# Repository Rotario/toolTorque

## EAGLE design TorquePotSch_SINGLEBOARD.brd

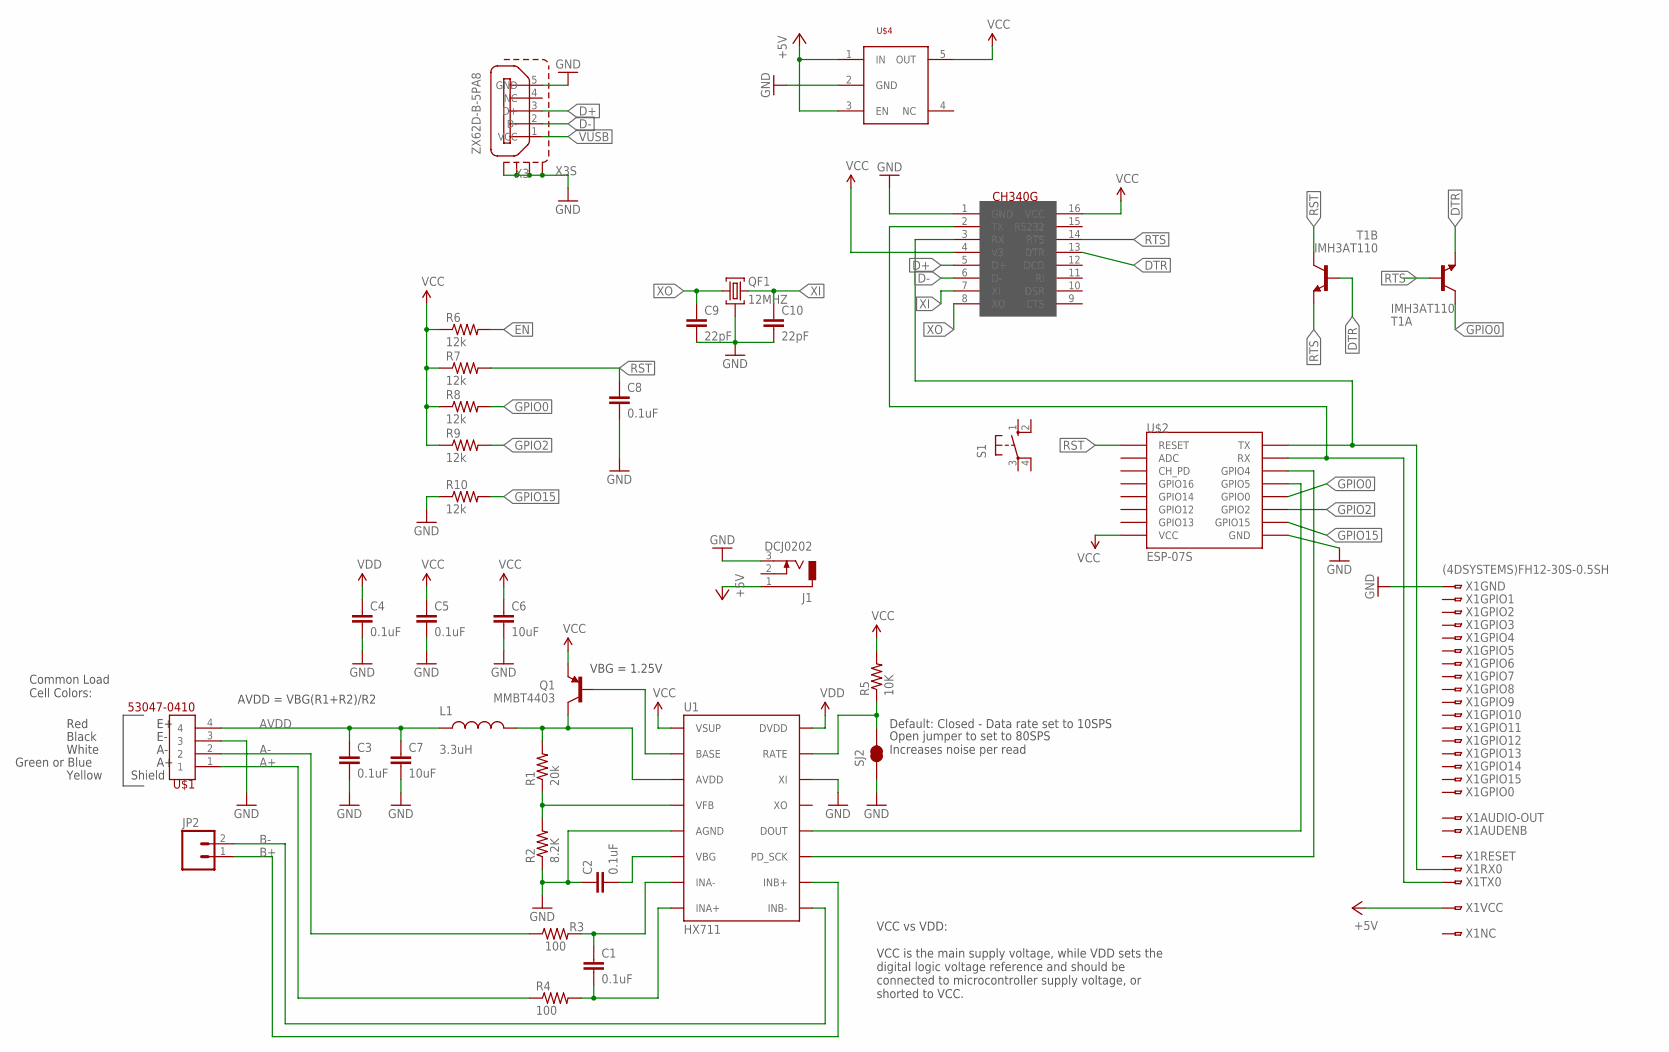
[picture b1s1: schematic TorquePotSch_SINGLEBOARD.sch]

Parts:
C1, C2, C3, C4, C5, C8: 0.1uF; 0603-CAP
C6, C7: 10uF; 1210
C9, C10: 22pF; 0603-CAP
J1: DCJ0202
JP2: M02PTH; 1X02
L1: 3.3uH; 0805
Q1: MMBT4403; SOT23-3
QF1: 12MHZ; HC49U
R1: 20k; 0603-RES
R2: 8.2K; 0603-RES
R3, R4: 100; 0603-RES
R5: 10K; 0603-RES
R6, R7, R8, R9, R10: 12k; R0805
S1: 10-XX; B3F-10XX
SJ2: JUMPER-PAD-2-NC_BY_TRACE; PAD-JUMPER-2-NC_BY_TRACE_YES_SILK
T1: IMH3AT110; SMT6
U1: HX711; SO16
U$1: 53047-0410
U$2: ESP-07S; ESP07S
U$3: CH340G; SOIC16
U$4: TLV755P; SOT23-5L
X1: (4DSYSTEMS)FH12-30S-0.5SH; FH12-30S-0.5SH
X3: ZX62D-B-5PA8

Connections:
+5V: J1.1, U$4.1 (IN), U$4.3 (EN), X1.26, X1.27
A+: R4.1, U$1.1
A-: R3.1, U$1.2
AVDD: C3.1, C7.1, L1.1, U$1.4
B+: JP2.1, U1.10 (INB+)
B-: JP2.2, U1.9 (INB-)
D+: U$3.5 (D+), X3.3 (D+)
D-: U$3.6 (D-), X3.2 (D-)
DTR: T1.6 (E), U$3.13 (DTR)
EN: R6.2
GND: C2.1, C3.2, C4.2, C5.2, C6.2, C7.2, C8.2, C9.2, C10.2, J1.3, QF1.2, R2.1, R10.1, SJ2.1, U1.5 (AGND), U1.14 (XI), U$1.3, U$2.GND, U$3.1 (GND), U$4.2 (GND), X1.1, X1.21, X1.25, X1.30, X3.5 (GND), X3.S1, X3.S2, X3.S3, X3.S4
GPIO0: R8.2, T1.1 (C), U$2.GPIO0
GPIO2: R9.2, U$2.GPIO2
GPIO15: R10.2, U$2.GPIO15
unnamed: R5.1, SJ2.2, U1.15 (RATE)
unnamed: C1.1, R3.2, U1.7 (INA-)
unnamed: C1.2, R4.2, U1.8 (INA+)
unnamed: Q1.1 (B), U1.2 (BASE)
unnamed: L1.2, Q1.3 (C), R1.2, U1.3 (AVDD)
unnamed: R1.1, R2.2, U1.4 (VFB)
unnamed: C2.2, U1.6 (VBG)
unnamed: U1.12 (DOUT), U$2.GPIO5
unnamed: U1.11 (PD_SCK), U$2.GPIO4
unnamed: U$2.TX, U$3.3 (RX), X1.23
unnamed: U$2.RX, U$3.2 (TX), X1.24
RST: C8.1, R7.2, U$2.REST (RESET)
RTS: U$3.14 (RTS)
VCC: C5.1, C6.1, Q1.2 (E), R5.2, R6.1, R7.1, R8.1, R9.1, U1.1 (VSUP), U$2.VCC, U$3.4 (V3), U$3.16 (VCC), U$4.5 (OUT)
VDD: C4.1, U1.16 (DVDD)
VUSB: X3.1 (VCC)
XI: C10.1, QF1.3, U$3.7 (XI)
XO: C9.1, QF1.1, U$3.8 (XO)

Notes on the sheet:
VBG = 1.25V
AVDD = VBG(R1+R2)/R2
Default: Closed - Data rate set to 10SPS
Open jumper to set to 80SPS Increases noise per read
Red
Black
White
Green or Blue
Common Load Cell Colors:
Shield
Yellow
VCC vs VDD: VCC is the main supply voltage, while VDD sets the digital logic voltage reference and should be connected to microcontroller supply voltage, or shorted to VCC.

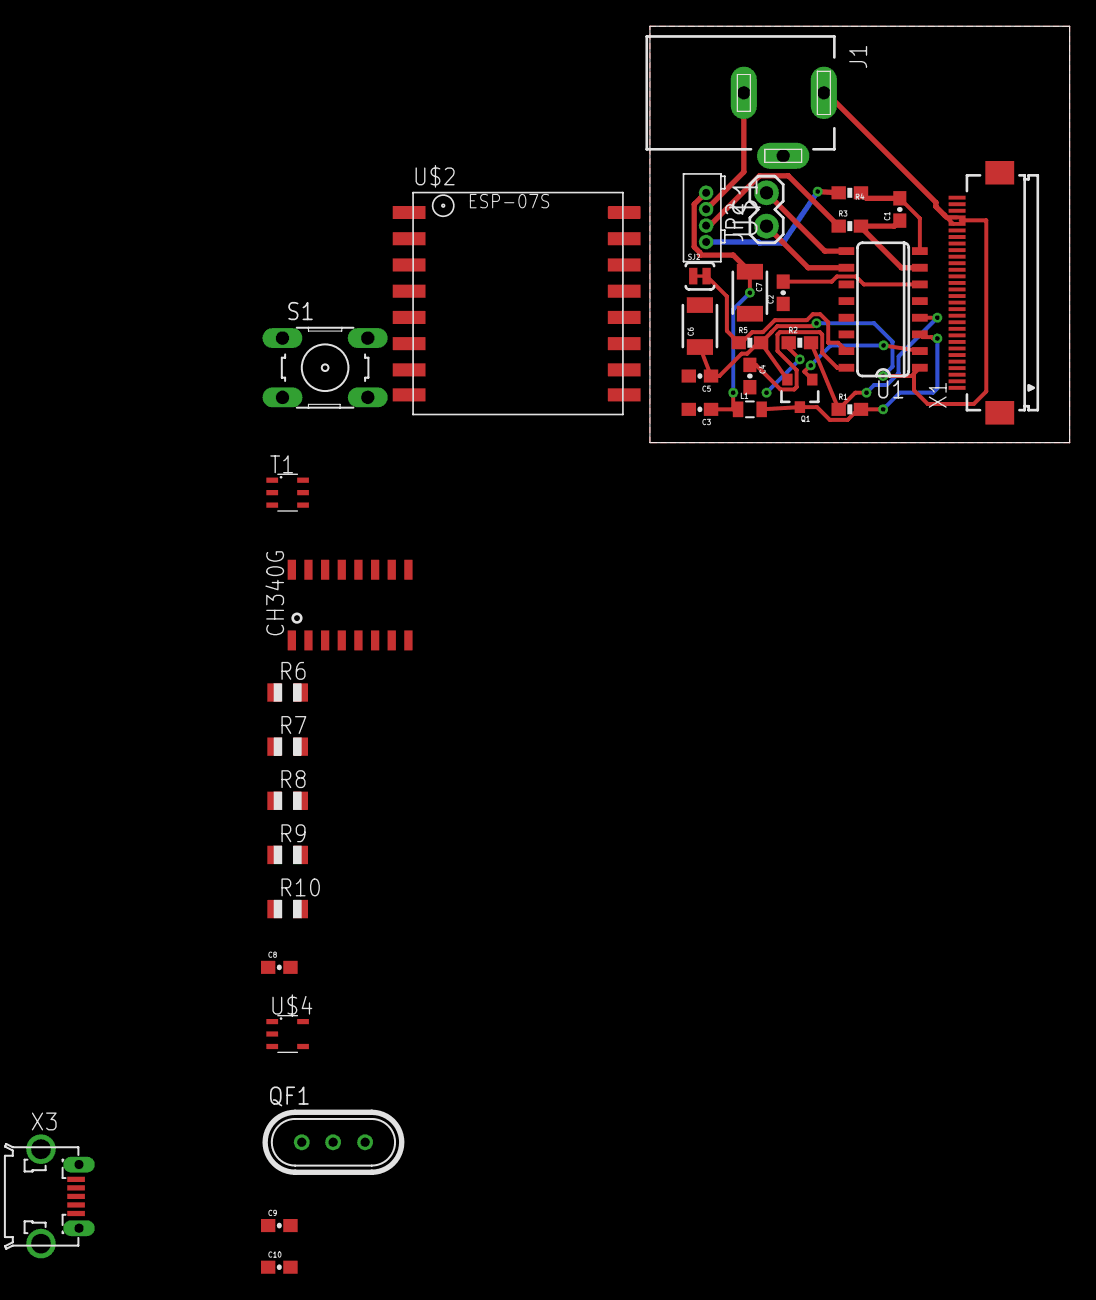
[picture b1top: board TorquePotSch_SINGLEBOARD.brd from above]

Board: 2 copper layers, 32.0 x 31.8 mm, 35 parts (0 on the bottom side), 29 nets.

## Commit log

2019-12-05 initial

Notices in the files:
parts and their libraries:
SparkFun-Capacitors: Licensing: Creative Commons ShareAlike 4.0 International - https://creativecommons.org/licenses/by-sa/4.0
SparkFun-Connectors: Licensing: CC v3.0 Share-Alike You are welcome to use this library for commercial purposes.
